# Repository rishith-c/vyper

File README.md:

# VYPER

VYPER is a parametric, Neptune-4-printable, rocket-body FPV quadcopter concept
with a true-X arm layout and rear-facing pusher propellers. It is inspired by
the packaging and drag-reduction approach of high-speed record drones such as
[Peregreen V4](https://airshaper.com/cases/peregreen-v4-fastest-drone); it is
not a copy and it is not a speed-record claim.

| Screening result | Current value |
|---|---:|
| Estimated all-up mass | 715 g |
| Static thrust-to-weight estimate | 8.8:1 |
| Analytical CdA build-up | 40.0 cm² |
| Target speed | 200 km/h, unproven |
| Ideal 5-inch prop pitch speed | 241 km/h |
| Required pitch efficiency at target | 83% |
| Fuselage envelope | Ø57 × 360 mm including tail |
| OrcaSlicer PETG mass | 257.1 g |

The speed result is an analytical feasibility screen, not CFD and not flight
data. Only two-direction radar or validated high-rate GNSS testing can establish
the aircraft's real speed.

## Repository contents

- `vyper_shell.py`: parameterized shell, split nose, four printed arms,
  internal hub, removable vertical electronics cassette and retained boat-tail.
- `vyper_assembly.py`: fit-check assembly with the selected battery, motors,
  props, board envelopes, camera/VTX/RX and exact M3×8 STEP fasteners.
- `stl/` and `cad/`: regenerated printable STL and STEP files.
- `test_vyper.py`: solid, fit, clearance, fastener, mass and first-order aero
  checks.
- `pcb/`: VYPER-F4 FC floorplan plus the VYPER-55A custom ESC EVT architecture,
  authored netlists, true-footprint unrouted review board and independent tests.
- `docs/BOM.md`: current purchased-part envelopes, budget and sourcing status.
- `docs/VALIDATION_GATES.md`: the tests required before LiPo power and flight.

```bash
source .venv/bin/activate
python test_vyper.py
python pcb/test_vyper_f4.py
python pcb/test_vyper_f4_netlist.py
python pcb/test_vyper_f4_drc.py
python pcb/test_vyper_esc.py
python pcb/test_vyper_esc_netlist.py
python firmware/am32/test_target.py
python vyper_shell.py
python vyper_assembly.py
python render_vyper.py
```

## Geometry

The center body is not two crossed chopsticks. It is a hollow Ø57 mm body of
revolution with a Von Kármán ogive, a removable cosine boat-tail and four
separate swept blade arms at 45/135/225/315 degrees. The motor pads remain
normal to the flight axis, so arm sweep does not cant thrust. Motors and props
are on the aft faces in pusher configuration.

Each 8×26 mm printed arm contains a Ø5.5 mm motor-wire bore. Adjacent 5-inch
prop discs have 28.6 mm tip clearance and clear the body by 18.0 mm. The 81×39×33
mm 6S battery has 0.96 mm radial fit allowance in the 53 mm internal diameter.

## Electronics status

Two paths are intentionally separated:

1. The under-$200 prototype budget uses a purchased 6S F405/55–60 A stack.
   That is the only sensible path for initial restrained and low-speed tests.
2. The custom FC and custom four-channel ESC are development boards. The FC is
   presently a validated 30×64 mm R3 vertical floorplan plus a 58-net / 77-component
   authored design and true-footprint four-layer review board. All 58 passives
   are in-outline, and all 250 nodes reach pads without placement/copper DRC
   errors, but 192 connections remain unrouted. It includes the ICM-42688-P,
   BMP280, blackbox, voltage/current sensing, external compass/GPS interfaces,
   and a level-shifted addressable RGB status LED. The reviewed graphical
   schematic is also open. The ESC has a validated 36×72 mm R3 vertical
   floorplan with 52 modeled major/support courtyards, a 159-net / 195-component authored electrical
   design, an AM32 target, and a six-layer true-footprint review board. All 715 authored
   netlist nodes reach physical pads, but KiCad correctly reports 499 unrouted
   connections. Neither custom board is orderable or flight-qualified yet.

The custom ESC's 55 A label is a **2-second design target**, not a tested
continuous rating. See [`pcb/FC_ARCHITECTURE.md`](pcb/FC_ARCHITECTURE.md) and
[`pcb/ESC_ARCHITECTURE.md`](pcb/ESC_ARCHITECTURE.md).

| ESC MOSFET / cooling face | ESC control / support face |
|---|---|
|  |  |

| FC power / sensor face | FC interface face |
|---|---|
|  |  |

## Known blockers before a physical build

- Add and fit-check a camera optical window/fairing in the shell.
- Complete reviewed graphical schematics and both boards' routing, ERC/DRC and
  manufacturing outputs.
- Print and weigh coupons; G-code now estimates 257.1 g and 14 h 39 min, but
  real spool density, flow calibration and failed-print allowance remain.
- Print tolerance coupons and proof-load an arm before installing a motor.
- Validate cooling and switch-node transients inside the closed fuselage.

## Safety

This is an unflown prototype with four unguarded 5-inch propellers and a high-
energy 6S LiPo. Props stay off for configuration and low-energy electronics
work. Custom ESC bring-up starts on a current-limited bench supply, never a
LiPo. Follow [`docs/VALIDATION_GATES.md`](docs/VALIDATION_GATES.md) and local
aviation/radio rules.

MIT licensed.

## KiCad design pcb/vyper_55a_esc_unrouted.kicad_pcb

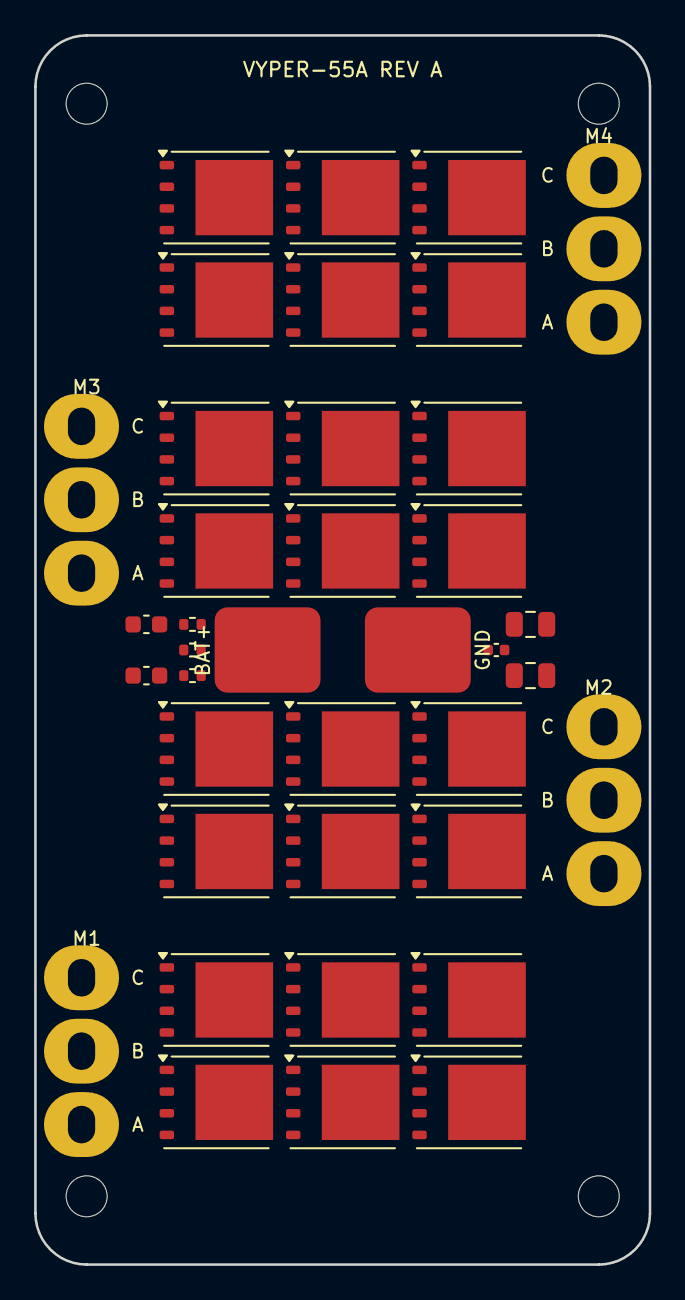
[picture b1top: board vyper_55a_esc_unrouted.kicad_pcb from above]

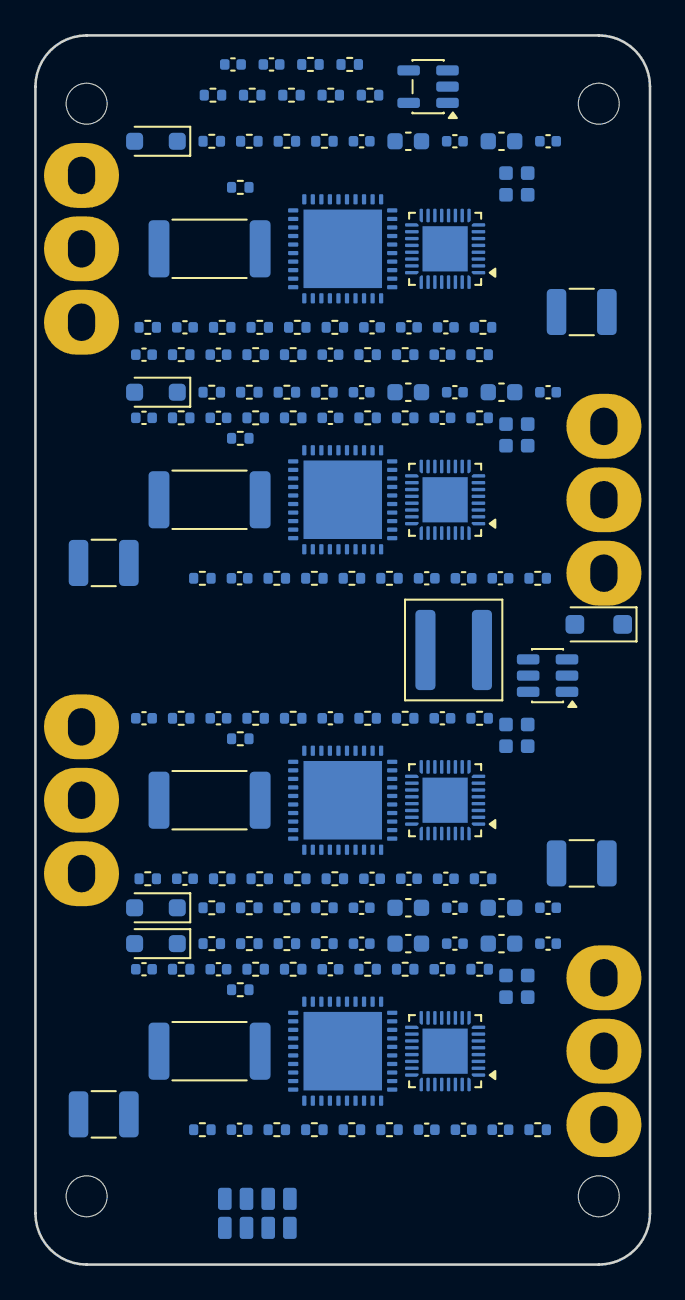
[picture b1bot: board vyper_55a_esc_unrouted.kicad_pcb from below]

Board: 6 copper layers, 36.0 x 72.0 mm, 199 parts (158 on the bottom side), 159 nets, no tracks yet.

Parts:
C1: 100nF 16V X7R; C_0402_1005Metric
C1A1, C1B1, C1C1, C2A1, C2B1, C2C1, C3A1, C3B1, C3C1, C4A1, C4B1, C4C1: 220pF C0G; C_0402_1005Metric
C1D1, C2D1, C3D1, C4D1: 1uF 6.3V X7R; C_0402_1005Metric
C1D2, C2D2, C3D2, C4D2: 100nF 100V X7R; C_0603_1608Metric
C1D3, C2D3, C3D3, C4D3: 10uF 50V X7R; C_1210_3225Metric
C1D4, C2D4, C3D4, C4D4: 47nF 100V X7R; C_0402_1005Metric
C1D5, C2D5, C3D5, C4D5: 1uF 25V X7R; C_0603_1608Metric
C1D6, C2D6, C3D6, C4D6: 100nF; C_0402_1005Metric
C1T1, C2T1, C3T1, C4T1: 10nF X7R; C_0402_1005Metric
C1V1, C2V1, C3V1, C4V1: 1nF C0G; C_0402_1005Metric
C2, C3: 2.2uF 100V X7R; C_0603_1608Metric
C4, C5: 22uF 10V X7R; C_0805_2012Metric
C101, C102, C201, C202, C301, C302, C401, C402: 100nF X7R; C_0402_1005Metric
C103, C203, C303, C403: 1uF X7R; C_0402_1005Metric
CS1: 100pF C0G; C_0402_1005Metric
CS2: 100nF X7R; C_0402_1005Metric
D1: PMEG6010CEH 60V 1A; D_SOD-123F
DT1, DT2, DT3, DT4: BAT54H; D_SOD-323_HandSoldering
FB1, FB2, FB3, FB4: 600R@100MHz; R_0402_1005Metric
H1, H2, H3, H4: M3_CLEAR
J1: FC_ESC_SH1.0_8P; FC_HARNESS_2X4_P1.27_SOLDER
J2: M1_SWD_PADS; SWD_2X2_P1.27_TESTPADS
J3: M2_SWD_PADS; SWD_2X2_P1.27_TESTPADS
J4: M3_SWD_PADS; SWD_2X2_P1.27_TESTPADS
J5: M4_SWD_PADS; SWD_2X2_P1.27_TESTPADS
JBAT: 12AWG_BATTERY_PIGTAIL; BATTERY_PIGTAIL_2X
JM1: M1_MOTOR_PADS; MOTOR_EDGE_PADS_3X
JM2: M2_MOTOR_PADS; MOTOR_EDGE_PADS_3X
JM3: M3_MOTOR_PADS; MOTOR_EDGE_PADS_3X
JM4: M4_MOTOR_PADS; MOTOR_EDGE_PADS_3X
L1: XGL5030-223MEC 22uH; L_Coilcraft_XAL5030-XXX
Q11, Q12, Q13, Q14, Q15, Q16, Q21, Q22, Q23, Q24, Q25, Q26, Q31, Q32, Q33, Q34, Q35, Q36, Q41, Q42, Q43, Q44, Q45, Q46: BSC012N06NS; TDSON-8-1
R1, R102, R202, R302, R402: 100k; R_0402_1005Metric
R1A1, R1B1, R1C1, R1V1, R2A1, R2B1, R2C1, R2V1, R3A1, R3B1, R3C1, R3V1, R4A1, R4B1, R4C1, R4V1: 100k 1% 50V; R_0402_1005Metric
R1A2, R1B2, R1C2, R1T1, R1V2, R2A2, R2B2, R2C2, R2T1, R2V2, R3A2, R3B2, R3C2, R3T1, R3V2, R4A2, R4B2, R4C2, R4T1, R4V2: 10k 1%; R_0402_1005Metric
R1D1, R2D1, R3D1, R4D1: 18k 5%; R_0402_1005Metric
R1D2, R2D2, R3D2, R4D2: 47k 5%; R_0402_1005Metric
R1D3, R1D4, R2D3, R2D4, R3D3, R3D4, R4D3, R4D4, R101, R201, R301, R401: 10k; R_0402_1005Metric
R2: 33.2k 1%; R_0402_1005Metric
R3: 10.0k 1%; R_0402_1005Metric
RS1, RS2, RS3, RS4: 10k 0.1%; R_0402_1005Metric
RS5: 10.0k 0.1%; R_0402_1005Metric
RS6: 30.1k 0.1%; R_0402_1005Metric
RSH1, RSH2, RSH3, RSH4: WSLF2512R0005FEA 0.5m 1% 10W; R_2512_6332Metric
RT1: 4.7k; R_0402_1005Metric
TH1, TH2, TH3, TH4: 10k B3435; R_0402_1005Metric
U1: LMR16006XDDCR; SOT-23-6
U2: TLV9061IDBVR; SOT-23-5
U11, U21, U31, U41: AT32F421K8U7-4; QFN-32-1EP_4x4mm_P0.4mm_EP2.65x2.65mm
U12, U22, U32, U42: DRV8323HRTAR; TI_RTA0040_WQFN40_6x6_P0.5_EP

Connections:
BUCK_CB: C1.1, U1.1
BUCK_EN: R1.2, U1.4
BUCK_FB: R2.2, R3.1, U1.3
BUCK_SW: C1.2, D1.1, L1.1, U1.6
CURRENT_AVERAGE: RS1.2, RS2.2, RS3.2, RS4.2, U2.3
CURRENT_SUM_FB: CS1.2, RS5.1, RS6.2, U2.4
DSHOT_M1: J1.5, U11.27
DSHOT_M2: J1.6, U21.27
DSHOT_M3: J1.7, U31.27
DSHOT_M4: J1.8, U41.27
ESC_CURRENT_TOTAL: CS1.1, J1.3, RS6.1, U2.1
ESC_TELEM: DT1.2, DT2.2, DT3.2, DT4.2, J1.4, RT1.1
M1_BEMF_A: C1A1.1, R1A1.2, R1A2.1, U11.6
M1_BEMF_B: C1B1.1, R1B1.2, R1B2.1, U11.10
M1_BEMF_C: C1C1.1, R1C1.2, R1C2.1, U11.11
M1_BOOT0: R102.1, U11.31
M1_CURRENT_ADC: RS1.1, U11.8, U12.23
M1_DRV_DVDD: C1D1.1, U12.33
M1_DRV_ENABLE: C1D6.1, R1D3.2, U12.30
M1_GATE_AH: Q11.4, U12.6
M1_GATE_AL: Q12.4, U12.8
M1_GATE_BH: Q13.4, U12.15
M1_GATE_BL: Q14.4, U12.13
M1_GATE_CH: Q15.4, U12.16
M1_GATE_CL: Q16.4, U12.18
M1_NFAULT: R1D4.1, U11.28, U12.25
M1_NRST: R101.1, U11.4
M1_NTC_ADC: C1T1.1, R1T1.2, TH1.1, U11.9
M1_PHASE_A: JM1.1, Q11.1, Q11.2, Q11.3, Q12.5, R1A1.1, U12.7
M1_PHASE_B: JM1.2, Q13.1, Q13.2, Q13.3, Q14.5, R1B1.1, U12.14
M1_PHASE_C: JM1.3, Q15.1, Q15.2, Q15.3, Q16.5, R1C1.1, U12.17
M1_POWER_RETURN: Q12.1, Q12.2, Q12.3, Q14.1, Q14.2, Q14.3, Q16.1, Q16.2, Q16.3, RSH1.1, U12.9
M1_PWM_AH: U11.20, U12.34
M1_PWM_AL: U11.15, U12.35
M1_PWM_BH: U11.19, U12.36
M1_PWM_BL: U11.14, U12.37
M1_PWM_CH: U11.18, U12.38
M1_PWM_CL: U11.13, U12.39
M1_VDDA: C103.1, FB1.2, U11.5
M1_VOLTAGE_ADC: C1V1.1, R1V1.2, R1V2.1, U11.12
M2_BEMF_A: C2A1.1, R2A1.2, R2A2.1, U21.6
M2_BEMF_B: C2B1.1, R2B1.2, R2B2.1, U21.10
M2_BEMF_C: C2C1.1, R2C1.2, R2C2.1, U21.11
M2_BOOT0: R202.1, U21.31
M2_CURRENT_ADC: RS2.1, U21.8, U22.23
M2_DRV_DVDD: C2D1.1, U22.33
M2_DRV_ENABLE: C2D6.1, R2D3.2, U22.30
M2_GATE_AH: Q21.4, U22.6
M2_GATE_AL: Q22.4, U22.8
M2_GATE_BH: Q23.4, U22.15
M2_GATE_BL: Q24.4, U22.13
M2_GATE_CH: Q25.4, U22.16
M2_GATE_CL: Q26.4, U22.18
M2_NFAULT: R2D4.1, U21.28, U22.25
M2_NRST: R201.1, U21.4
M2_NTC_ADC: C2T1.1, R2T1.2, TH2.1, U21.9
M2_PHASE_A: JM2.1, Q21.1, Q21.2, Q21.3, Q22.5, R2A1.1, U22.7
M2_PHASE_B: JM2.2, Q23.1, Q23.2, Q23.3, Q24.5, R2B1.1, U22.14
M2_PHASE_C: JM2.3, Q25.1, Q25.2, Q25.3, Q26.5, R2C1.1, U22.17
M2_POWER_RETURN: Q22.1, Q22.2, Q22.3, Q24.1, Q24.2, Q24.3, Q26.1, Q26.2, Q26.3, RSH2.1, U22.9
M2_PWM_AH: U21.20, U22.34
M2_PWM_AL: U21.15, U22.35
M2_PWM_BH: U21.19, U22.36
M2_PWM_BL: U21.14, U22.37
M2_PWM_CH: U21.18, U22.38
M2_PWM_CL: U21.13, U22.39
M2_VDDA: C203.1, FB2.2, U21.5
M2_VOLTAGE_ADC: C2V1.1, R2V1.2, R2V2.1, U21.12
M3_BEMF_A: C3A1.1, R3A1.2, R3A2.1, U31.6
M3_BEMF_B: C3B1.1, R3B1.2, R3B2.1, U31.10
M3_BEMF_C: C3C1.1, R3C1.2, R3C2.1, U31.11
M3_BOOT0: R302.1, U31.31
M3_CURRENT_ADC: RS3.1, U31.8, U32.23
M3_DRV_DVDD: C3D1.1, U32.33
M3_DRV_ENABLE: C3D6.1, R3D3.2, U32.30
M3_GATE_AH: Q31.4, U32.6
M3_GATE_AL: Q32.4, U32.8
M3_GATE_BH: Q33.4, U32.15
M3_GATE_BL: Q34.4, U32.13
M3_GATE_CH: Q35.4, U32.16
M3_GATE_CL: Q36.4, U32.18
M3_NFAULT: R3D4.1, U31.28, U32.25
M3_NRST: R301.1, U31.4
M3_NTC_ADC: C3T1.1, R3T1.2, TH3.1, U31.9
M3_PHASE_A: JM3.1, Q31.1, Q31.2, Q31.3, Q32.5, R3A1.1, U32.7
M3_PHASE_B: JM3.2, Q33.1, Q33.2, Q33.3, Q34.5, R3B1.1, U32.14
M3_PHASE_C: JM3.3, Q35.1, Q35.2, Q35.3, Q36.5, R3C1.1, U32.17
M3_POWER_RETURN: Q32.1, Q32.2, Q32.3, Q34.1, Q34.2, Q34.3, Q36.1, Q36.2, Q36.3, RSH3.1, U32.9
M3_PWM_AH: U31.20, U32.34
M3_PWM_AL: U31.15, U32.35
M3_PWM_BH: U31.19, U32.36
M3_PWM_BL: U31.14, U32.37
M3_PWM_CH: U31.18, U32.38
M3_PWM_CL: U31.13, U32.39
M3_VDDA: C303.1, FB3.2, U31.5
M3_VOLTAGE_ADC: C3V1.1, R3V1.2, R3V2.1, U31.12
M4_BEMF_A: C4A1.1, R4A1.2, R4A2.1, U41.6
M4_BEMF_B: C4B1.1, R4B1.2, R4B2.1, U41.10
M4_BEMF_C: C4C1.1, R4C1.2, R4C2.1, U41.11
M4_BOOT0: R402.1, U41.31
M4_CURRENT_ADC: RS4.1, U41.8, U42.23
M4_DRV_DVDD: C4D1.1, U42.33
M4_DRV_ENABLE: C4D6.1, R4D3.2, U42.30
M4_GATE_AH: Q41.4, U42.6
M4_GATE_AL: Q42.4, U42.8
M4_GATE_BH: Q43.4, U42.15
M4_GATE_BL: Q44.4, U42.13
M4_GATE_CH: Q45.4, U42.16
M4_GATE_CL: Q46.4, U42.18
M4_NFAULT: R4D4.1, U41.28, U42.25
M4_NRST: R401.1, U41.4
M4_NTC_ADC: C4T1.1, R4T1.2, TH4.1, U41.9
M4_PHASE_A: JM4.1, Q41.1, Q41.2, Q41.3, Q42.5, R4A1.1, U42.7
M4_PHASE_B: JM4.2, Q43.1, Q43.2, Q43.3, Q44.5, R4B1.1, U42.14
M4_PHASE_C: JM4.3, Q45.1, Q45.2, Q45.3, Q46.5, R4C1.1, U42.17
M4_POWER_RETURN: Q42.1, Q42.2, Q42.3, Q44.1, Q44.2, Q44.3, Q46.1, Q46.2, Q46.3, RSH4.1, U42.9
M4_PWM_AH: U41.20, U42.34
M4_PWM_AL: U41.15, U42.35
M4_PWM_BH: U41.19, U42.36
M4_PWM_BL: U41.14, U42.37
M4_PWM_CH: U41.18, U42.38
M4_PWM_CL: U41.13, U42.39
M4_VDDA: C403.1, FB4.2, U41.5
M4_VOLTAGE_ADC: C4V1.1, R4V1.2, R4V2.1, U41.12
unnamed: J2.2, U11.23
unnamed: J2.3, U11.24
unnamed: C1D4.1, U12.2
unnamed: C1D4.2, U12.1
unnamed: C1D5.1, U12.3
unnamed: R1D1.1, U12.28
unnamed: R1D2.1, U12.29
unnamed: DT1.1, U11.29
unnamed: J3.2, U21.23
unnamed: J3.3, U21.24
unnamed: C2D4.1, U22.2
unnamed: C2D4.2, U22.1
unnamed: C2D5.1, U22.3
unnamed: R2D1.1, U22.28
unnamed: R2D2.1, U22.29
unnamed: DT2.1, U21.29
unnamed: J4.2, U31.23
unnamed: J4.3, U31.24
unnamed: C3D4.1, U32.2
unnamed: C3D4.2, U32.1
unnamed: C3D5.1, U32.3
unnamed: R3D1.1, U32.28
unnamed: R3D2.1, U32.29
unnamed: DT3.1, U31.29
unnamed: J5.2, U41.23
unnamed: J5.3, U41.24
unnamed: C4D4.1, U42.2
unnamed: C4D4.2, U42.1
unnamed: C4D5.1, U42.3
unnamed: R4D1.1, U42.28
unnamed: R4D2.1, U42.29
unnamed: DT4.1, U41.29
PGND: C1A1.2, C1B1.2, C1C1.2, C1D1.2, C1D2.2, C1D3.2, C1D6.2, C1T1.2, C1V1.2, C2.2, C2A1.2, C2B1.2, C2C1.2, C2D1.2, C2D2.2, C2D3.2, C2D6.2, C2T1.2, C2V1.2, C3.2, C3A1.2, C3B1.2, C3C1.2, C3D1.2, C3D2.2, C3D3.2, C3D6.2, C3T1.2, C3V1.2, C4.2, C4A1.2, C4B1.2, C4C1.2, C4D1.2, C4D2.2, C4D3.2, C4D6.2, C4T1.2, C4V1.2, C5.2, C101.2, C102.2, C103.2, C201.2, C202.2, C203.2, C301.2, C302.2, C303.2, C401.2, C402.2, C403.2, CS2.2, D1.2, J1.1, J2.4, J3.4, J4.4, J5.4, JBAT.2, R1A2.2, R1B2.2, R1C2.2, R1D1.2, R1D2.2, R1V2.2, R2A2.2, R2B2.2, R2C2.2, R2D1.2, R2D2.2, R2V2.2, R3.2, R3A2.2, R3B2.2, R3C2.2, R3D1.2, R3D2.2, R3V2.2, R4A2.2, R4B2.2, R4C2.2, R4D1.2, R4D2.2, R4V2.2, R102.2, R202.2, R302.2, R402.2, RS5.2, RSH1.2, RSH2.2, RSH3.2, RSH4.2, TH1.2, TH2.2, TH3.2, TH4.2, U1.2, U2.2, U11.33, U12.10, U12.11, U12.12, U12.19, U12.20, U12.24, U12.26, U12.31, U12.32, U12.40, U12.41, U21.33, U22.10, U22.11, U22.12, U22.19, U22.20, U22.24, U22.26, U22.31, U22.32, U22.40, U22.41, U31.33, U32.10, U32.11, U32.12, U32.19, U32.20, U32.24, U32.26, U32.31, U32.32, U32.40, U32.41, U41.33, U42.10, U42.11, U42.12, U42.19, U42.20, U42.24, U42.26, U42.31, U42.32, U42.40, U42.41
V3V3_ESC: C4.1, C5.1, C101.1, C102.1, C201.1, C202.1, C301.1, C302.1, C401.1, C402.1, CS2.1, FB1.1, FB2.1, FB3.1, FB4.1, J2.1, J3.1, J4.1, J5.1, L1.2, R1D3.1, R1D4.2, R1T1.1, R2.1, R2D3.1, R2D4.2, R2T1.1, R3D3.1, R3D4.2, R3T1.1, R4D3.1, R4D4.2, R4T1.1, R101.2, R201.2, R301.2, R401.2, RT1.2, U2.5, U11.1, U11.17, U21.1, U21.17, U31.1, U31.17, U41.1, U41.17
VBAT_6S: C1D2.1, C1D3.1, C1D5.2, C2.1, C2D2.1, C2D3.1, C2D5.2, C3.1, C3D2.1, C3D3.1, C3D5.2, C4D2.1, C4D3.1, C4D5.2, J1.2, JBAT.1, Q11.5, Q13.5, Q15.5, Q21.5, Q23.5, Q25.5, Q31.5, Q33.5, Q35.5, Q41.5, Q43.5, Q45.5, R1.1, R1V1.1, R2V1.1, R3V1.1, R4V1.1, U1.5, U12.4, U12.5, U22.4, U22.5, U32.4, U32.5, U42.4, U42.5

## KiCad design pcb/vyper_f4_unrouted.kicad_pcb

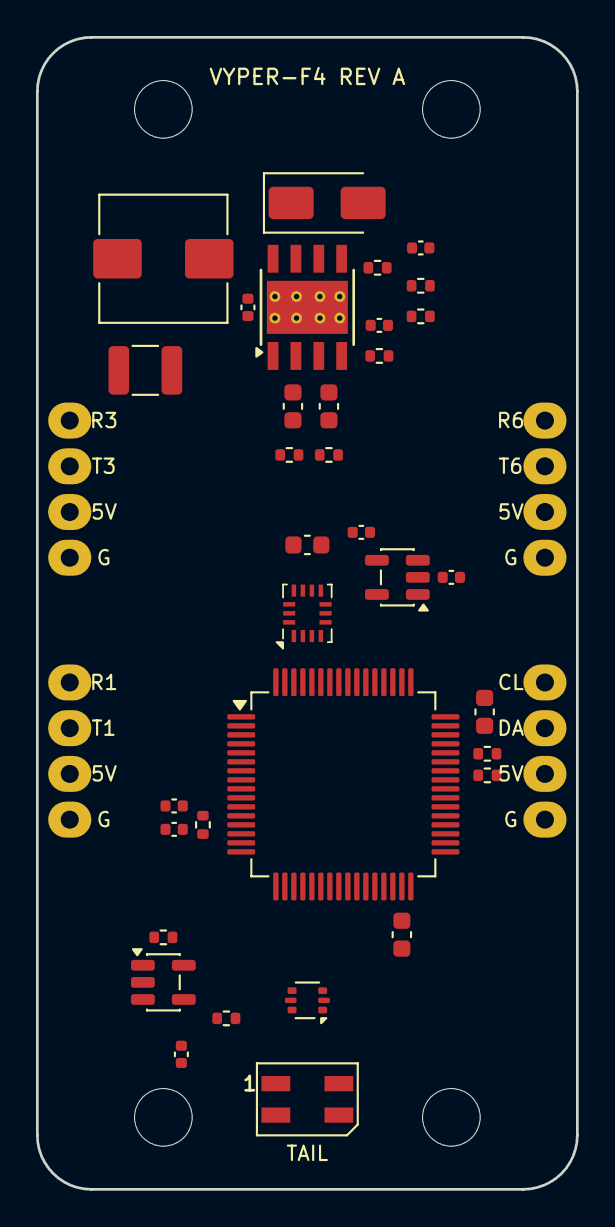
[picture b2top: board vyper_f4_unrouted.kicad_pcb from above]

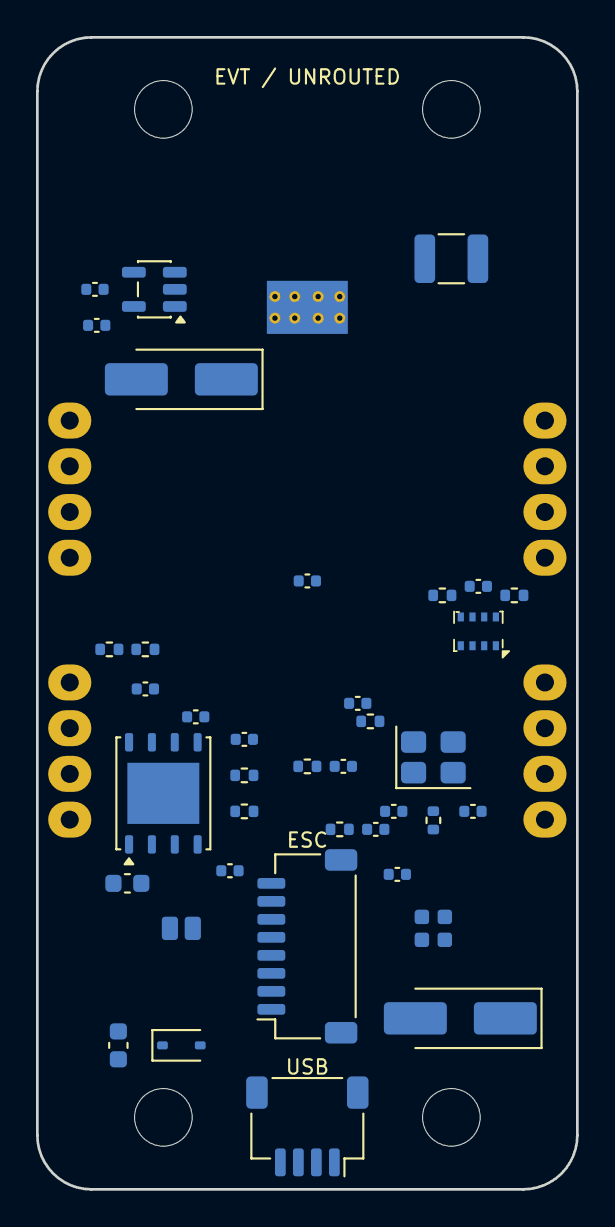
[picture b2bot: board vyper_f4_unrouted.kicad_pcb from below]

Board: 4 copper layers, 30.0 x 64.0 mm, 80 parts (38 on the bottom side), 58 nets, no tracks yet.

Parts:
C1: 6.8nF C0G; C_0402_1005Metric
C2: 39pF C0G; C_0402_1005Metric
C3: 100nF 16V X7R; C_0402_1005Metric
C4, C6: 2.2uF 100V X7R; C_0603_1608Metric
C5, C7: 47uF 10V X7R; C_1210_3225Metric
C8, C9, C10, C11: 1uF 10V X7R; C_0402_1005Metric
C12, C14, C15, C16, C17, C24, C31: 100nF X7R; C_0402_1005Metric
C13: 1uF X7R; C_0402_1005Metric
C18: 4.7uF X7R; C_0603_1608Metric
C19, C20: 2.2uF low-ESR; C_0603_1608Metric
C21, C22: 18pF C0G; C_0402_1005Metric
C23, C26, C27: 100nF; C_0402_1005Metric
C25: 2.2uF X7R; C_0603_1608Metric
C28: 1uF 10V; C_0603_1608Metric
C29, C30: 10nF C0G; C_0402_1005Metric
D1: B560C 60V 5A; D_SMA
D2, D3: SS14; D_SMA_Handsoldering
D4: SK6812MINI-E; LED_SK6812MINI_PLCC4_3.5x3.5mm_P1.75mm
D7: PESD5V low-C; D_SOD-323
FB1: 600R@100MHz; R_0402_1005Metric
H1, H2, H3, H4: MTG_M3_grommet
J1: USB_SERVICE_SH1.0_4P; JST_SH_SM04B-SRSS-TB_1x04-1MP_P1.00mm_Horizontal
J2: ESC_SH1.0_8P; JST_SH_SM08B-SRSS-TB_1x08-1MP_P1.00mm_Horizontal
J3: RX_UART1; J3_SOLDER_PADS
J4: GPS_UART3; J4_SOLDER_PADS
J5: EXTERNAL_I2C; J5_SOLDER_PADS
J6: VTX_UART6; J6_SOLDER_PADS
J7: SWD; J7_SOLDER_PADS
J8: BEEPER_PAD; J8_SOLDER_PADS
L1: 8.2uH Isat>=5.8A; L_Wuerth_HCI-7050
R1: 162k 1%; R_0402_1005Metric
R2: 523k 1%; R_0402_1005Metric
R3: 84.5k 1%; R_0402_1005Metric
R4: 53.6k 1%; R_0402_1005Metric
R5: 10.2k 1%; R_0402_1005Metric
R6: 13.0k 1%; R_0402_1005Metric
R7: 1M; R_0402_1005Metric
R8, R10, R11: 10k; R_0402_1005Metric
R9, R20: 100k; R_0402_1005Metric
R12, R13: 4.7k; R_0402_1005Metric
R14, R15: ERJ2RKF22R0X 22R 1%; R_0402_1005Metric
R16: 100k 0.1%; R_0402_1005Metric
R17: 10k 0.1%; R_0402_1005Metric
R18: 1k; R_0402_1005Metric
R19: 33R; R_0402_1005Metric
U1: STM32F405RGTx; LQFP-64_10x10mm_P0.5mm
U2: ICM-42688-P; Bosch_LGA-14_3x2.5mm_P0.5mm
U3: TPS54360DDA; TI_SO-PowerPAD-8_ThermalVias
U4, U5: AP2112K-3.3; SOT-23-5
U6: W25Q128JVPIM; WDFN-8-1EP_6x5mm_P1.27mm_EP3.4x4mm
U7: BMP280; Bosch_LGA-8_2x2.5mm_P0.65mm_ClockwisePinNumbering
U8: SN74AHCT1G125DBVR; SOT-23-5
U9: USBLC6-2SC6; SOT-666
Y1: 8MHz 10pF; Crystal_SMD_3225-4Pin_3.2x2.5mm

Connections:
ADC_CURRENT: C30.1, R18.2, U1.11
ADC_VBAT: C29.1, R16.2, R17.1, U1.25
BEEPER: J8.2, U1.2
BOOT0: R9.1, U1.60
BUCK_BOOT: C3.1, U3.1
BUCK_COMP_MID: C2.1, R6.1, U3.6
BUCK_COMP_RC: C1.1, R6.2
BUCK_EN: R2.2, R3.1, U3.3
BUCK_FB: R4.2, R5.1, U3.5
BUCK_RT: R1.1, U3.4
BUCK_SW: C3.2, D1.1, L1.1, U3.8
ESC_CURRENT: J2.3, R18.1
ESC_TELEM: J2.4, U1.54
FLASH_CS: U1.33, U6.1
FLASH_HOLD_N: R11.1, U6.7
FLASH_WP_N: R10.1, U6.3
GND: C1.2, C2.2, C4.2, C5.2, C6.2, C7.2, C8.2, C9.2, C10.2, C11.2, C12.2, C13.2, C14.2, C15.2, C16.2, C17.2, C18.2, C19.2, C20.2, C21.2, C22.2, C23.2, C24.2, C25.2, C26.2, C27.2, C28.2, C29.2, C30.2, C31.2, D1.2, D4.2, D7.1, J1.1, J2.1, J3.1, J4.1, J5.1, J6.1, J7.4, R1.2, R3.2, R5.2, R9.2, R17.2, R20.2, U1.12, U1.18, U1.63, U2.6, U2.7, U2.9, U3.7, U3.9, U4.2, U5.2, U6.4, U7.1, U7.5, U7.7, U8.1, U8.3, U9.2
GPS_UART3_RX: J4.4, U1.30
GPS_UART3_TX: J4.3, U1.29
GYRO_CS: U1.59, U2.12
GYRO_INT1: U1.58, U2.4
HSE_IN: C21.1, R7.1, U1.5, Y1.1
HSE_OUT: C22.1, R7.2, U1.6, Y1.2
I2C1_SCL: J5.4, R12.1, U1.61, U7.4
I2C1_SDA: J5.3, R13.1, U1.62, U7.3
LED_RGB_DIN: D4.3, R19.2
LED_RGB_LEVEL: R19.1, U8.4
LED_RGB_MCU: R20.1, U1.41, U8.2
LOGIC_IN: C8.1, C10.1, D2.1, D3.1, U4.1, U4.3, U5.1, U5.3
MOTOR_1: J2.5, U1.27
MOTOR_2: J2.6, U1.26
MOTOR_3: J2.7, U1.17
MOTOR_4: J2.8, U1.16
NRST: C23.1, R8.1, U1.7
RX_UART1_RX: J3.4, U1.43
RX_UART1_TX: J3.3, U1.42
SPI1_MISO: U1.56, U2.1
SPI1_MOSI: U1.57, U2.14
SPI1_SCK: U1.55, U2.13
SPI2_MISO: U1.35, U6.2
SPI2_MOSI: U1.36, U6.5
SPI2_SCK: U1.34, U6.6
SWCLK: J7.3, U1.49
SWDIO: J7.2, U1.46
USB_5V: C28.1, D3.2, D7.2, J1.2, U9.5
USB_DM: R14.2, U1.44
USB_DM_RAW: J1.4, R14.1, U9.3, U9.4
USB_DP: R15.2, U1.45
USB_DP_RAW: J1.3, R15.1, U9.1, U9.6
V3V3: C9.1, C14.1, C15.1, C16.1, C17.1, C18.1, C26.1, C27.1, FB1.1, J7.1, R8.2, R10.2, R11.2, R12.2, R13.2, U1.1, U1.19, U1.32, U1.48, U1.64, U4.5, U6.8, U7.2, U7.6, U7.8
V3V3_A: C12.1, C13.1, FB1.2, U1.13
V3V3_GYRO: C11.1, C24.1, C25.1, U2.5, U2.8, U5.5
V5_BUCK: C5.1, C7.1, C31.1, D2.2, D4.4, J3.2, J4.2, J5.2, J6.2, J8.1, L1.2, R4.1, U8.5
VBAT_6S: C4.1, C6.1, J2.2, R2.1, R16.1, U3.2
VCAP1: C19.1, U1.31
VCAP2: C20.1, U1.47
VTX_UART6_RX: J6.4, U1.38
VTX_UART6_TX: J6.3, U1.37

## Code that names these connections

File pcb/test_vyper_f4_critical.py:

"""Verify the manually routed VYPER-F4 critical-network stage.

This is a routing-stage gate, not a fabrication release test. It proves that
the compact buck, gyro, clock, regulator and analog-supply copper did not
introduce hard DRC errors or silently lengthen critical nets.
"""

import json
import os
import shutil
import subprocess
import tempfile
from collections import defaultdict
from pathlib import Path

import pcbnew

HERE = Path(__file__).resolve().parent
BOARD = HERE / "vyper_f4_critical.kicad_pcb"
DEFAULT_MAC_CLI = Path("/Applications/KiCad.app/Contents/MacOS/kicad-cli")

board = pcbnew.LoadBoard(str(BOARD))
stats = defaultdict(lambda: {"length": 0.0, "segments": 0,
                             "vias": 0, "layers": set()})
for item in board.GetTracks():
    entry = stats[item.GetNetname()]
    entry["length"] += pcbnew.ToMM(item.GetLength())
    entry["segments"] += 1
    entry["layers"].add(board.GetLayerName(item.GetLayer()))
    if isinstance(item, pcbnew.PCB_VIA):
        entry["vias"] += 1
        minimum_via = (0.60 if item.GetNetname() in {
            "SPI1_SCK", "SPI1_MISO", "SPI1_MOSI",
            "HSE_IN", "HSE_OUT"} else 0.65)
        assert pcbnew.ToMM(item.GetWidth(pcbnew.F_Cu)) >= minimum_via
        assert pcbnew.ToMM(item.GetDrillValue()) >= 0.30

assert stats["BUCK_SW"]["length"] <= 11.0
assert stats["BUCK_SW"]["vias"] == 0
assert stats["BUCK_SW"]["layers"] == {"F.Cu"}
assert stats["BUCK_BOOT"]["length"] <= 3.0
assert stats["BUCK_BOOT"]["vias"] == 0
assert stats["VBAT_6S"]["length"] <= 4.2
assert stats["VBAT_6S"]["vias"] == 0
assert stats["V5_BUCK"]["length"] <= 8.0
assert stats["V5_BUCK"]["vias"] == 1

for net_name in ("GYRO_CS", "GYRO_INT1", "SPI1_SCK", "SPI1_MISO",
                 "SPI1_MOSI"):
    assert stats[net_name]["length"] <= 10.0, (
        net_name, stats[net_name]["length"])
assert stats["GYRO_CS"]["vias"] == 0
assert stats["GYRO_INT1"]["vias"] == 0
for net_name in ("SPI1_SCK", "SPI1_MISO", "SPI1_MOSI"):
    assert stats[net_name]["vias"] == 2
assert stats["SPI1_SCK"]["layers"] == {"F.Cu", "In2.Cu"}
assert stats["SPI1_MISO"]["layers"] == {"F.Cu", "B.Cu"}
assert stats["SPI1_MOSI"]["layers"] == {"F.Cu", "B.Cu"}
for net_name in ("HSE_IN", "HSE_OUT"):
    assert stats[net_name]["length"] <= 13.0
    assert stats[net_name]["vias"] == 1
    assert stats[net_name]["layers"] == {"F.Cu", "B.Cu"}
assert stats["LOGIC_IN"]["length"] <= 4.0
assert stats["LOGIC_IN"]["vias"] == 0
assert stats["V3V3_GYRO"]["length"] <= 21.0
assert stats["V3V3_GYRO"]["vias"] == 1
assert stats["VCAP1"]["length"] <= 4.0
assert stats["VCAP1"]["vias"] == 0
assert stats["VCAP1"]["layers"] == {"F.Cu"}
assert stats["VCAP2"]["length"] <= 2.2
assert stats["VCAP2"]["vias"] == 0
assert stats["VCAP2"]["layers"] == {"F.Cu"}
assert stats["V3V3_A"]["length"] <= 8.0
assert stats["V3V3_A"]["vias"] == 0
assert stats["V3V3_A"]["layers"] == {"F.Cu"}
assert stats["V3V3"]["vias"] == 8
assert stats["BOOT0"]["length"] <= 9.0
assert stats["BOOT0"]["vias"] == 1
assert stats["BOOT0"]["layers"] == {"F.Cu", "B.Cu"}
assert stats["NRST"]["length"] <= 18.5
assert stats["NRST"]["vias"] == 2
assert stats["NRST"]["layers"] == {"F.Cu", "In2.Cu", "B.Cu"}

# USB FS source stubs stay on the component side. Both protected conductors
# use identical via counts and layer sets, and their complete MCU-to-harness
# copper lengths remain matched after the intentional D+ tail serpentine.
assert stats["USB_DM"]["length"] <= 3.0
assert stats["USB_DP"]["length"] <= 2.6
for net_name in ("USB_DM", "USB_DP"):
    assert stats[net_name]["vias"] == 0
    assert stats[net_name]["layers"] == {"F.Cu"}
for net_name in ("USB_DM_RAW", "USB_DP_RAW"):
    assert stats[net_name]["length"] <= 36.5
    assert stats[net_name]["vias"] == 2
    assert stats[net_name]["layers"] == {"F.Cu", "In2.Cu", "B.Cu"}
usb_dm_total = stats["USB_DM"]["length"] + stats["USB_DM_RAW"]["length"]
usb_dp_total = stats["USB_DP"]["length"] + stats["USB_DP_RAW"]["length"]
assert abs(usb_dm_total - usb_dp_total) <= 0.50
assert stats["USB_5V"]["length"] <= 35.0
assert stats["USB_5V"]["vias"] == 1
assert stats["USB_5V"]["layers"] == {"F.Cu", "B.Cu"}

zones = list(board.Zones())
assert len(zones) == 2
zone_contract = {(zone.GetNetname(), zone.GetLayer()) for zone in zones}
assert zone_contract == {("GND", pcbnew.In1_Cu),
                         ("V3V3", pcbnew.In2_Cu)}
assert all(zone.IsFilled() for zone in zones)

cli = os.environ.get("KICAD_CLI") or shutil.which("kicad-cli")
if not cli and DEFAULT_MAC_CLI.exists():
    cli = str(DEFAULT_MAC_CLI)
if not cli:
    raise SystemExit("kicad-cli not found; set KICAD_CLI")

with tempfile.NamedTemporaryFile(suffix=".json") as report:
    subprocess.run([cli, "pcb", "drc", "--format", "json", "--severity-all",
                    "--output", report.name, str(BOARD)],
                   check=False, capture_output=True, text=True)
    drc = json.loads(Path(report.name).read_text())

allowed = {"lib_footprint_issues", "silk_over_copper", "silk_overlap",
           "silk_edge_clearance", "text_height"}
hard = [item for item in drc["violations"] if item["type"] not in allowed]
assert not hard, [(item["type"], item["description"]) for item in hard]
assert len(drc["unconnected_items"]) == 105

print("critical buck routing has zero hard DRC violations")
print("BUCK_SW 10.73 mm total tree, zero vias, F.Cu only")
print("BOOT/VBAT/V5 route-length and via-count gates pass")
print("all five gyro nets are <= 10 mm with controlled layer changes")
print("8 MHz HSE and dedicated gyro-regulator routes pass length/via gates")
print("both STM32 VCAP paths pass dedicated local-capacitor gates")
print("filled In1 GND and In2 3V3 planes plus VDDA island pass")
print("four local STM32 VDD bypass loops and bulk capacitor pass DRC")
print("BOOT0 and NRST startup networks pass route/via gates")
print("USB FS pair uses equal via/layer topology with <= 0.50 mm total skew")
print("105 items remain unrouted; board is NOT FOR FAB")

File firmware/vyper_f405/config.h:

/* VYPER-F4 Rev A Betaflight target resource contract.
 * Hardware must pass schematic/PCB review and bench bring-up before flight.
 */
#pragma once

#define FC_TARGET_MCU STM32F405
#define BOARD_NAME VYPERF405
#define MANUFACTURER_ID VYPR
#define SYSTEM_HSE_MHZ 8

#define USE_ACC
#define USE_GYRO
#define USE_GYRO_SPI_ICM42688P
#define USE_ACC_SPI_ICM42688P
#define USE_FLASH
#define USE_FLASH_W25Q128FV
#define USE_BARO
#define USE_BARO_BMP280
#ifndef USE_MAG
#define USE_MAG
#define USE_MAG_QMC5883
#define USE_MAG_LIS2MDL
#endif
#ifndef USE_GPS
#define USE_GPS
#endif

#define MOTOR1_PIN PB1
#define MOTOR2_PIN PB0
#define MOTOR3_PIN PA3
#define MOTOR4_PIN PA2
#define UART1_TX_PIN PA9
#define UART1_RX_PIN PA10
#define UART3_TX_PIN PB10
#define UART3_RX_PIN PB11
#define UART5_RX_PIN PD2
#define UART6_TX_PIN PC6
#define UART6_RX_PIN PC7
#define I2C1_SCL_PIN PB8
#define I2C1_SDA_PIN PB9
#define SPI1_SCK_PIN PB3
#define SPI1_SDI_PIN PB4
#define SPI1_SDO_PIN PB5
#define SPI2_SCK_PIN PB13
#define SPI2_SDI_PIN PB14
#define SPI2_SDO_PIN PB15
#define GYRO_1_CS_PIN PB7
#define GYRO_1_EXTI_PIN PB6
#define FLASH_CS_PIN PB12
#define ADC_VBAT_PIN PC5
#define ADC_CURR_PIN PC3
#define LED_STRIP_PIN PA8
#define BEEPER_PIN PC13

#define TIMER_PIN_MAPPING \
    TIMER_PIN_MAP(0, PB1, 2, 0) \
    TIMER_PIN_MAP(1, PB0, 2, 0) \
    TIMER_PIN_MAP(2, PA3, 1, 1) \
    TIMER_PIN_MAP(3, PA2, 1, 0) \
    TIMER_PIN_MAP(4, PA8, 2, 0)

#define ADC1_DMA_OPT 1
#define GYRO_1_SPI_INSTANCE SPI1
#define GYRO_1_ALIGN CW90_DEG
#define FLASH_SPI_INSTANCE SPI2
#define BARO_I2C_INSTANCE I2CDEV_1
#define MAG_I2C_INSTANCE I2CDEV_1
#define DEFAULT_BLACKBOX_DEVICE BLACKBOX_DEVICE_FLASH
#define DEFAULT_DSHOT_BURST DSHOT_DMAR_OFF
#define DEFAULT_DSHOT_BITBANG DSHOT_BITBANG_OFF
#define DEFAULT_CURRENT_METER_SOURCE CURRENT_METER_ADC
#define DEFAULT_VOLTAGE_METER_SOURCE VOLTAGE_METER_ADC
#define ESC_SENSOR_UART SERIAL_PORT_UART5
